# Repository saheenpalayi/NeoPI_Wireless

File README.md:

# Neoπ Wireless CNC Controller (3-axis) 

## Project Overview
This project was made for ESP32 based 3-Axis Milling Machines. I started this project During my time at the FAB LAB Kerala for an awesome project Called [FAB Neo](https://fab.cba.mit.edu/classes/865.21/people/rahul/) by Rahul s Rajan. He was developing an Open source fully compact easy to Use PCB Milling Machine Over the years.

## Fetures of Neoπ Wireless CNC Controller
- NodeMCU-32 ESP32 38 Pin  Board based Controller
- SD Card Supported
- A4988/DRV8825 and SPI TMC 2130 stepper Drivers supported
- Reverse Polarity Protection
- Over Voltage protection**
- 12v/24 compatible
- OTA Supports
- PWM Spindle Support
- 2 Probes available (PROB1 and PROB2)
- Power LED Indications RED(power) and Green (5V)

** Optional The board works even without this feature.

## Hardware Pin Mapping

| Sl No | Pin-Names | GPIO |
| --- | --- | --- |
| 1 | X_Dir | GPIO26 |
| 2 | X_Step | GPIO12 |
| 3 | Y_Dir | GPIO25 |
| 4 | Y_Step | GPIO14 |
| 5 | Z_Dir | GPIO33 |
| 6 | Z_Step | GPIO27 |
| 7 | X_limit | GPIO21 |
| 8 | Y_limit | GPIO4 |
| 9 | Z_limit | GPIO15 |
| 10 | Stepper_disable | GPIO13 |
| 11 | Spindle | GPIO17 |
| 12 | PB1 | GPIO32 |
| 13 | PB2 | GPIO22 |

## Firmware

- Use [Grbl_ESP32](https://github.com/bdring/Grbl_Esp32) with [NeoPI_W_v1.h](https://github.com/saheenpalayi/NeoPI_Wireless/blob/main/Firmware/NeoPI_W_v1.h) machine file

## Credits
The Grbl_ESP32 firmware and the ESP32 Hardware is a well-written Open source Project by [bdring](https://github.com/bdring) A K A Barton Dring.

I took reference from these two projects mentioned below
- [Grbl_ESP32_Development_Controller](https://github.com/bdring/Grbl_ESP32_Development_Controller)
- [A 4 axis ESP32 CNC controller for daisy chained SPI stepper drivers](https://github.com/bdring/4_Axis_SPI_CNC#revision-history)
## Revision History
**v1.0**
- version 1 is my first build it has some problems and fixes to do

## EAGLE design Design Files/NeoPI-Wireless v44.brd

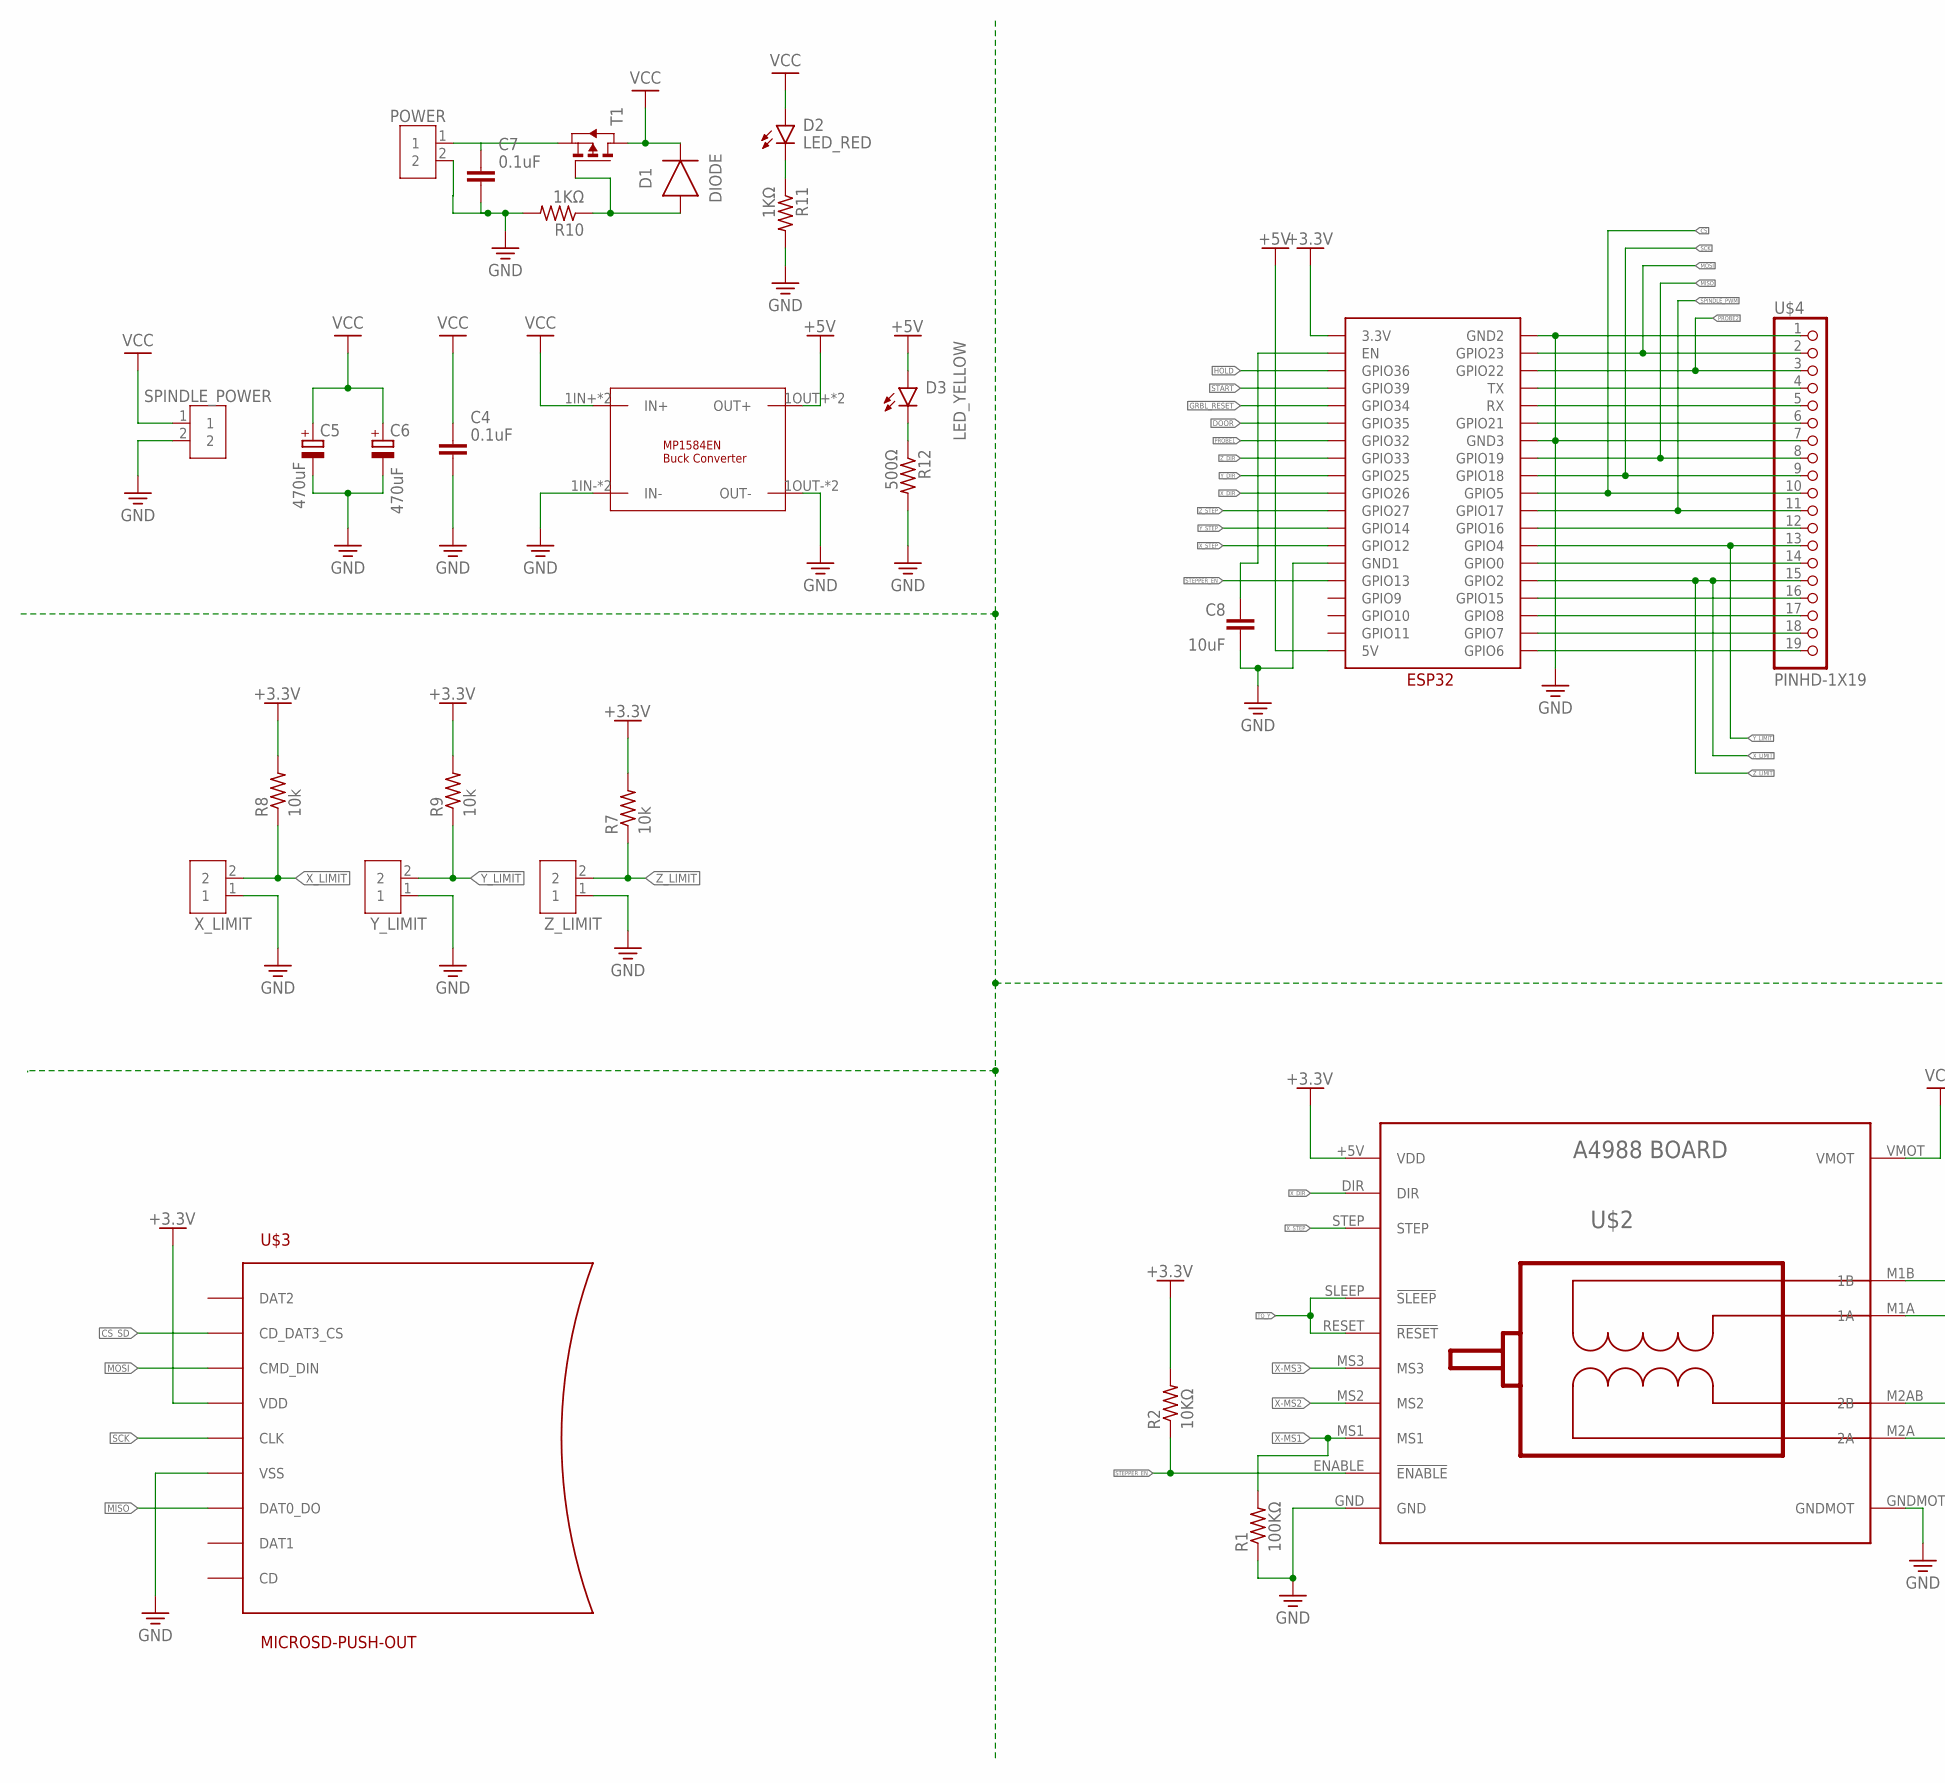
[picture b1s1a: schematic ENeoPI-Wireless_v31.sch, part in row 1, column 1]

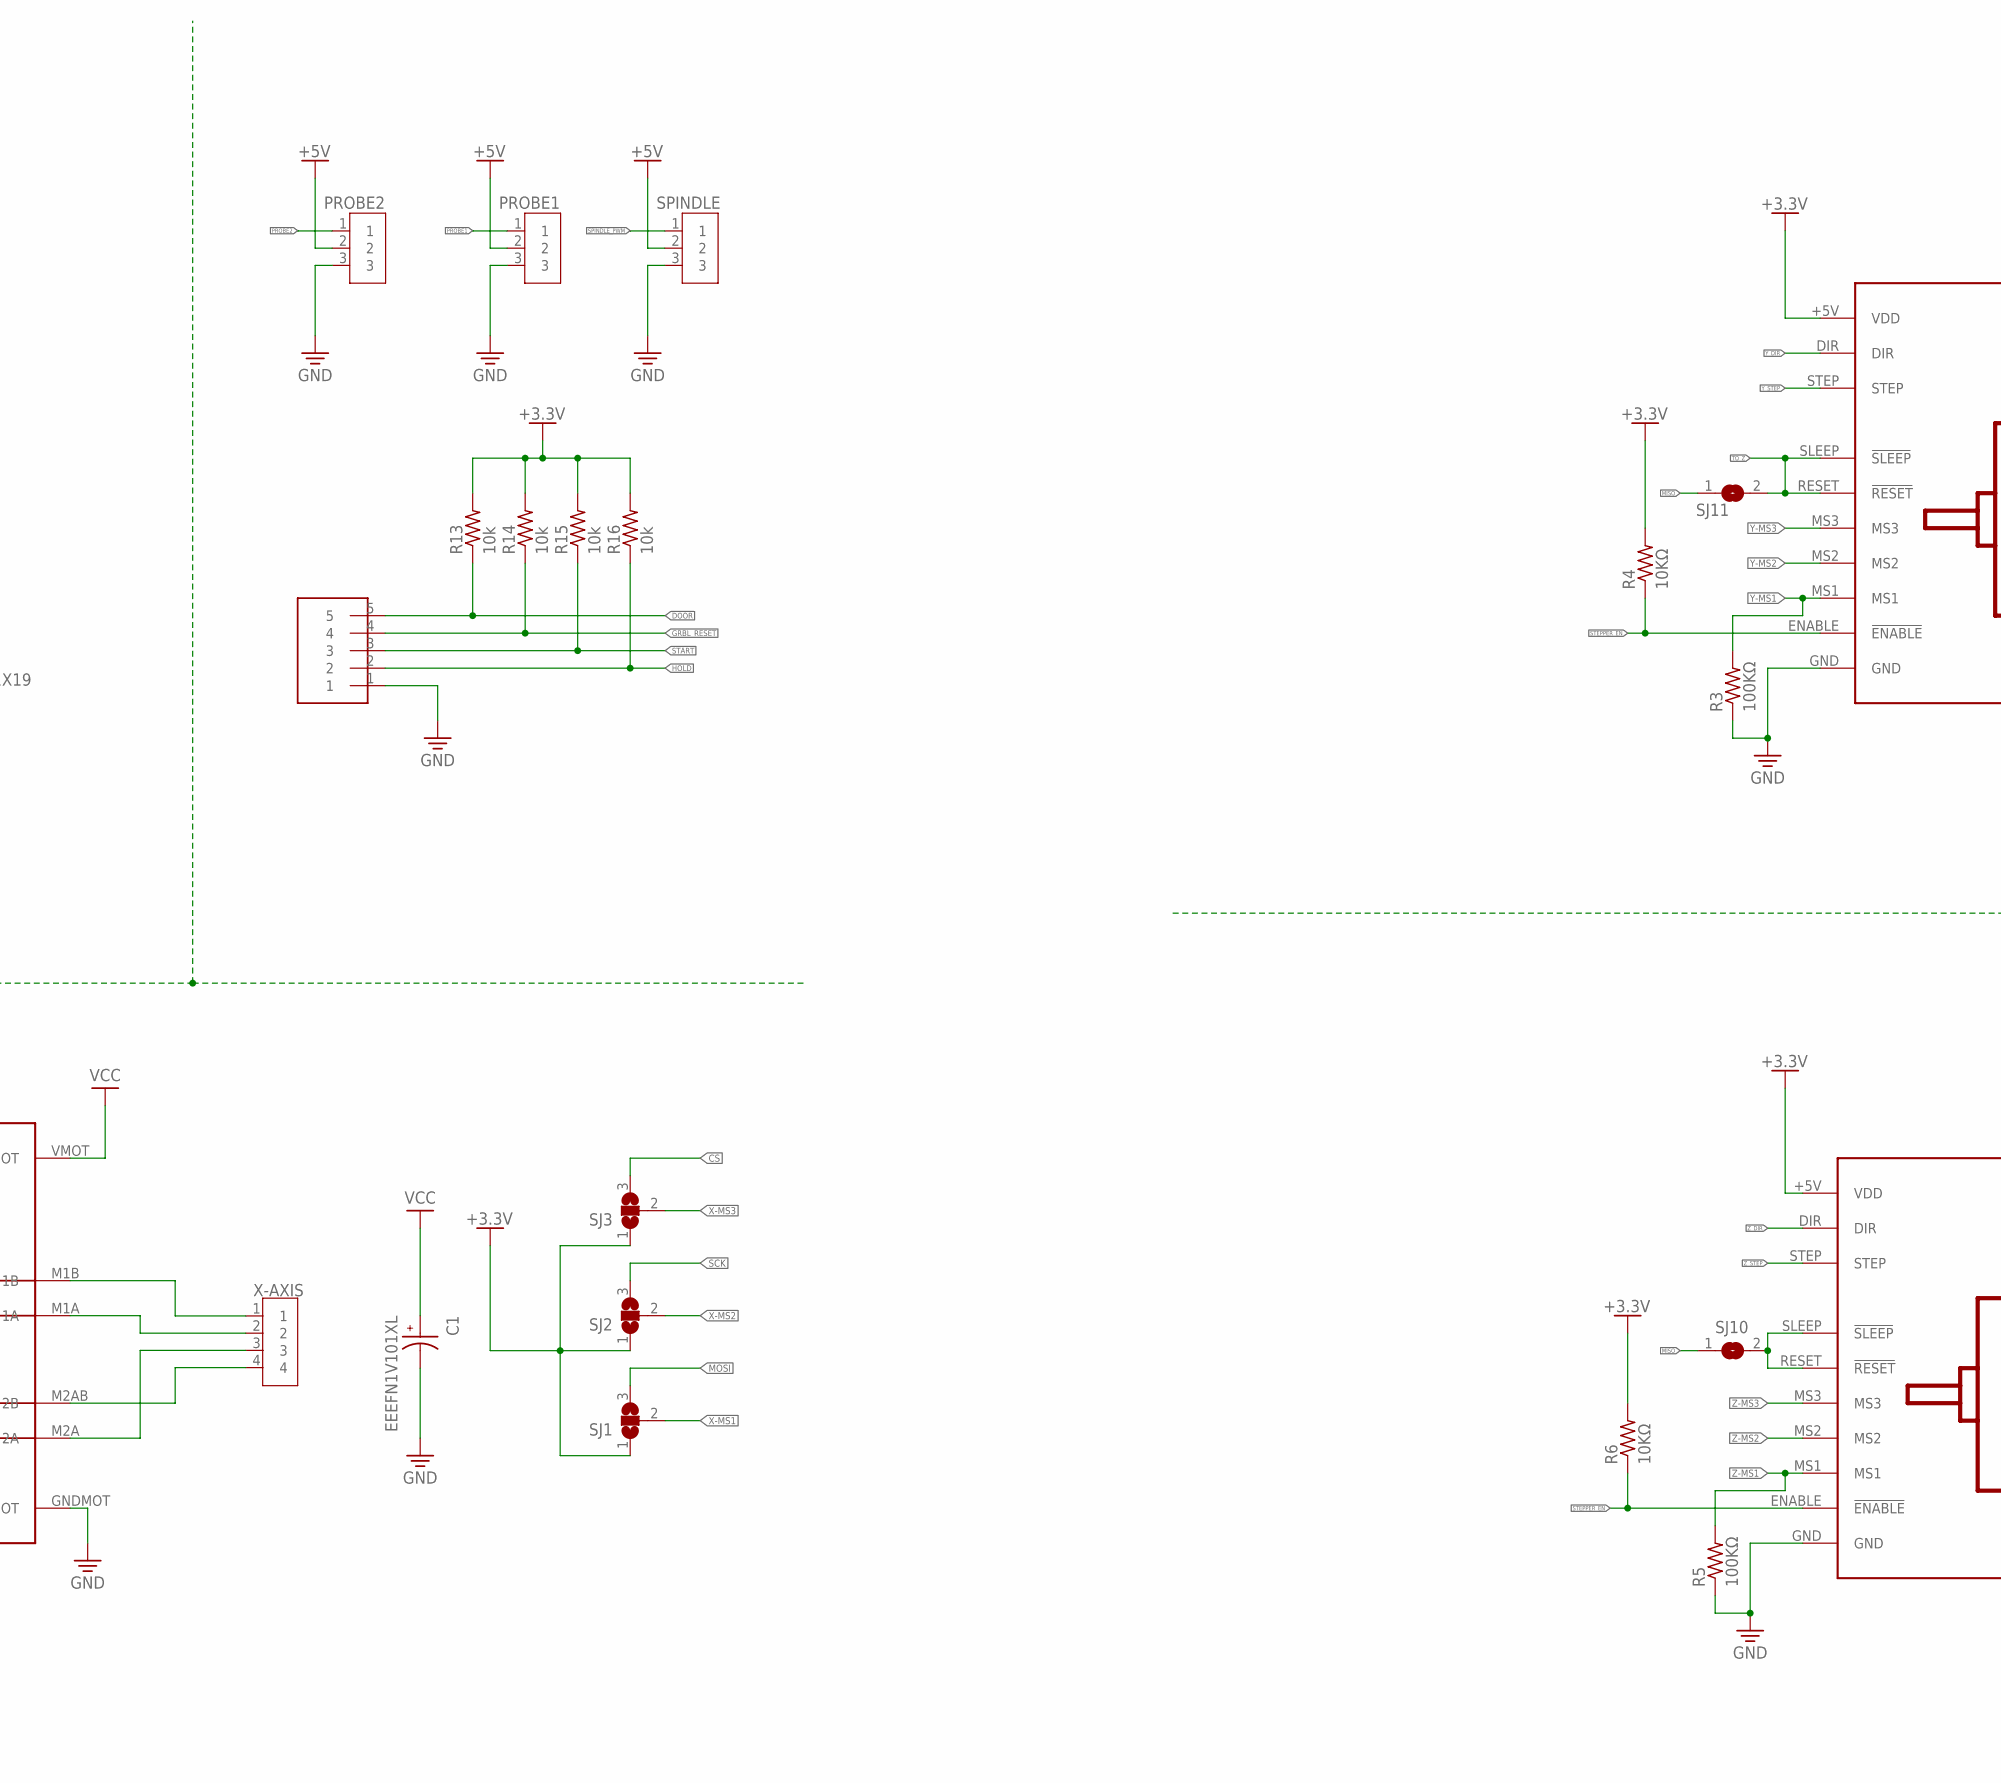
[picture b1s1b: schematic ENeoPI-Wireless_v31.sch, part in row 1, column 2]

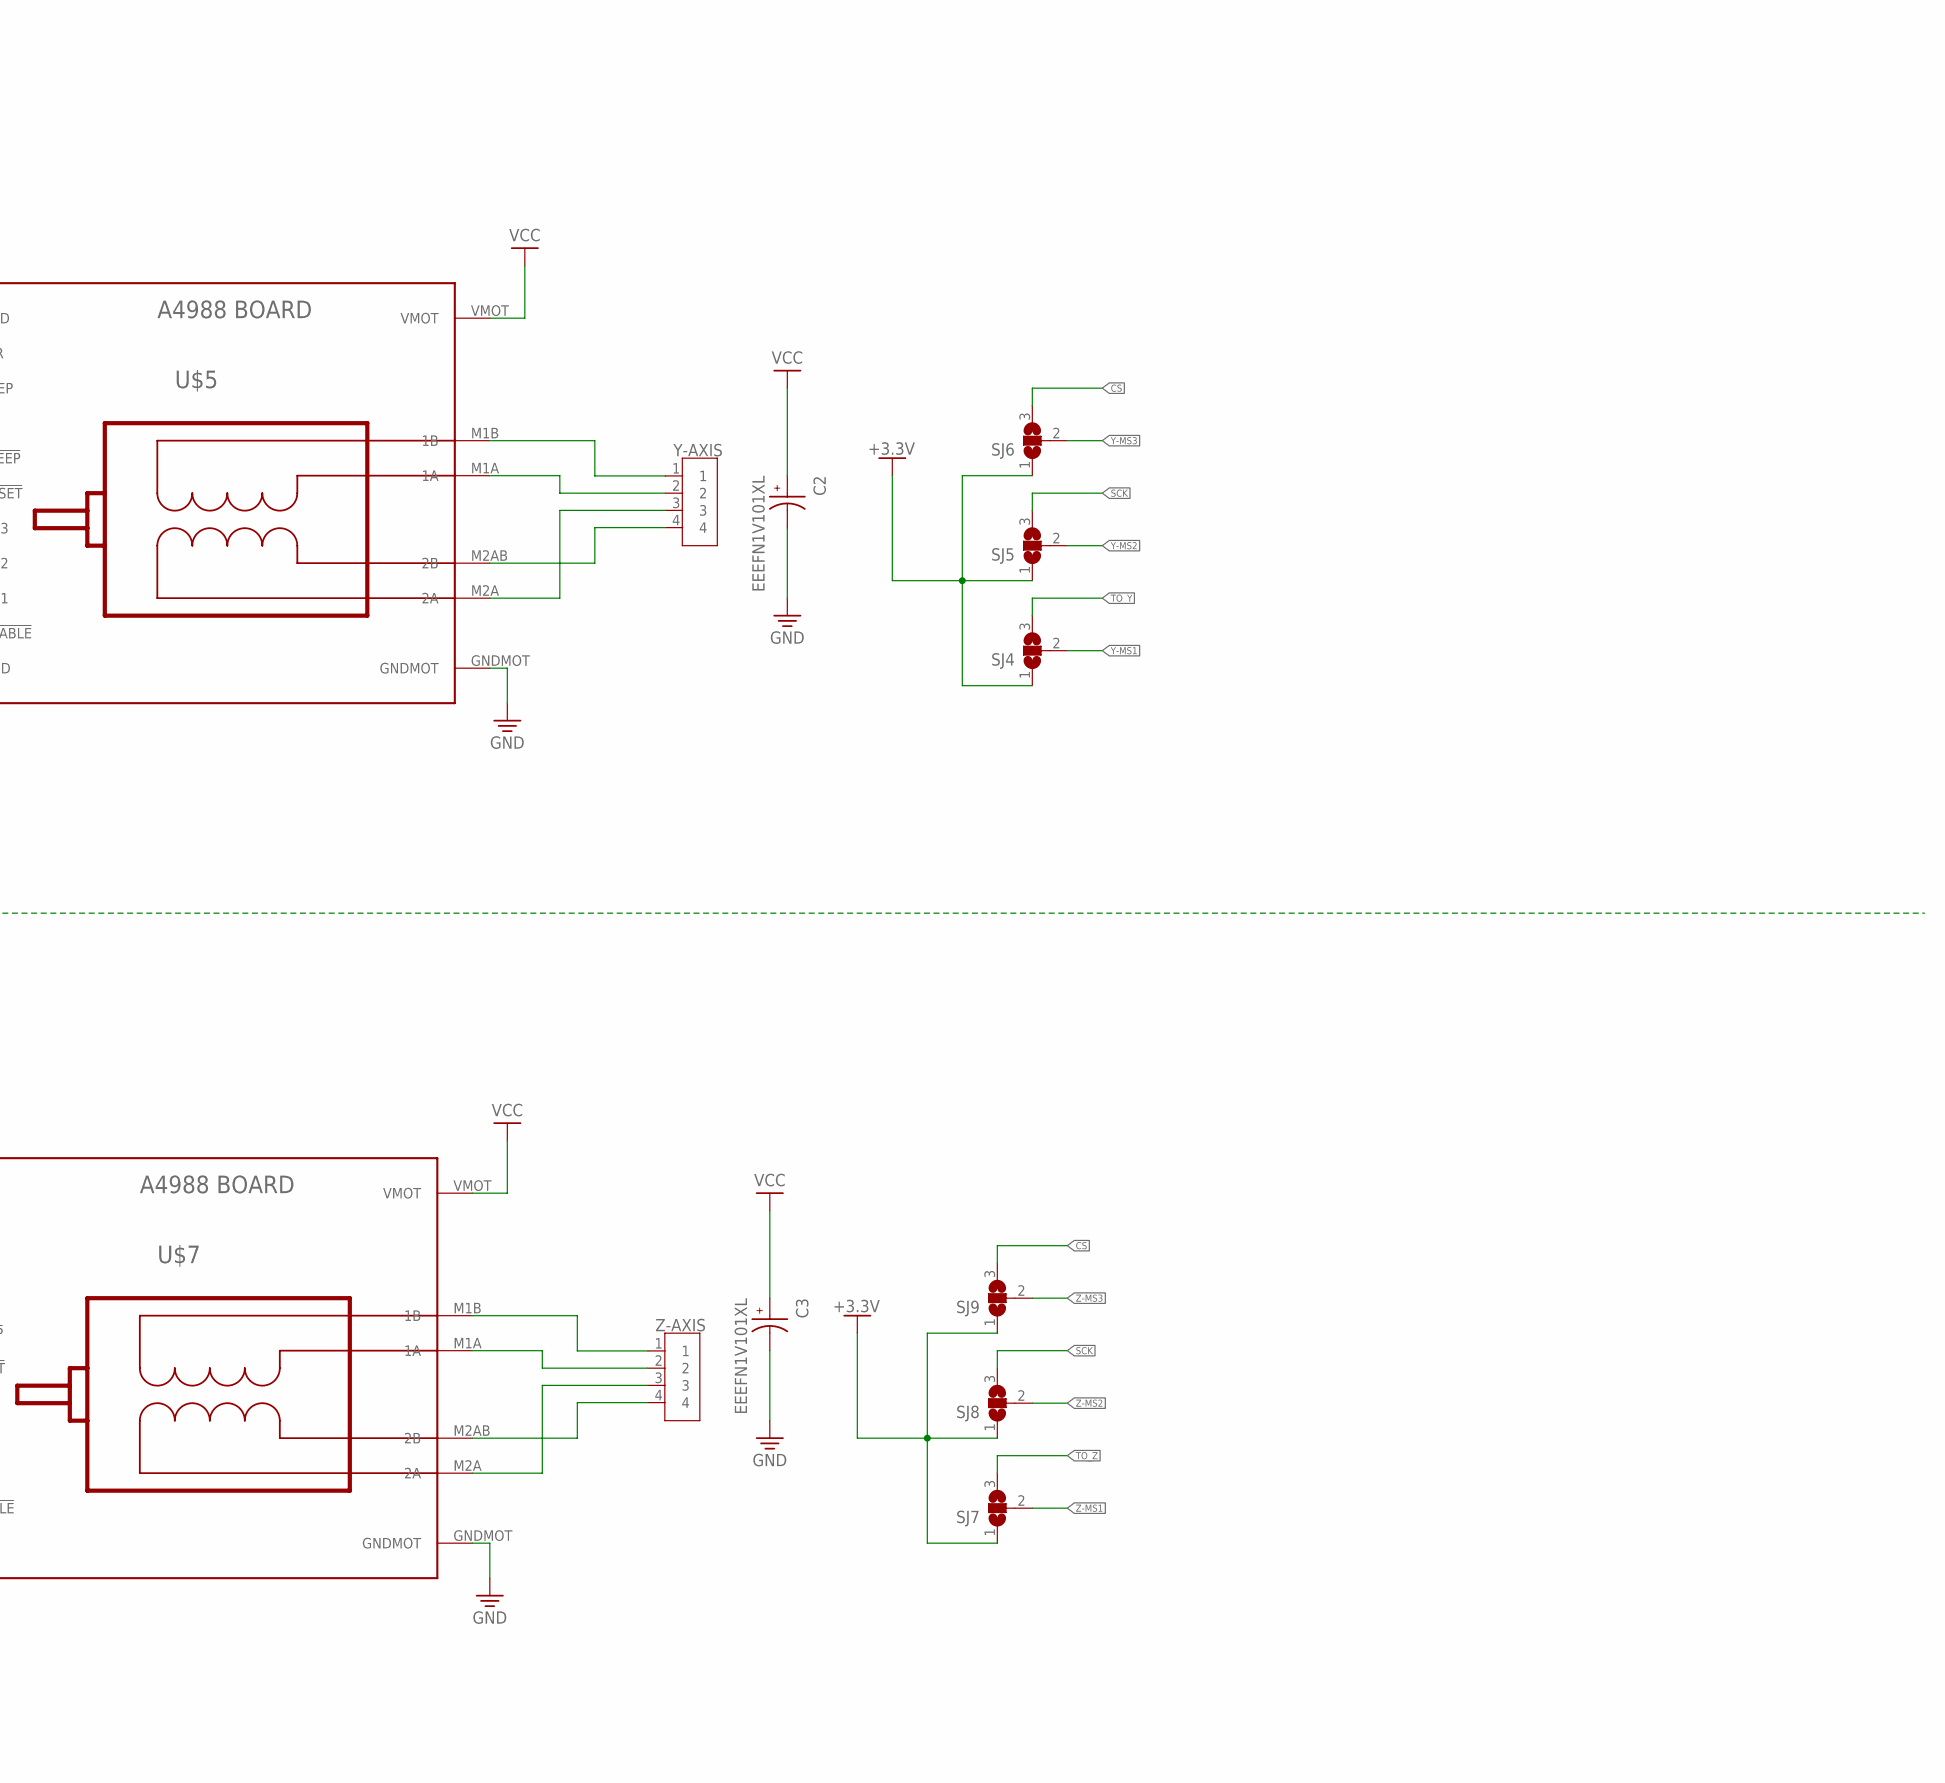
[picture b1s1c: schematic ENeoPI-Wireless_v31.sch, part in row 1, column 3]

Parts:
C1, C2, C3: EEEFN1V101XL; CAP_EEEFN1V101XL
C4, C7: 0.1uF; CAPC3216X135
C5, C6: 470uF; CAPAE1030X1050N
C8: 10uF; CAPC3216X135
D1: DIODE; DIOMELF5024
D2: LED_RED; LEDC3216X75N_FLAT-R
D3: LED_YELLOW; LEDC3216X75N_FLAT-Y
POWER: 2828XX-2282837-2; TERMBLK_508-2N
PROBE1, PROBE2: 2828XX-3282834-3; TERMBLK_254-3N
R1, R3, R5: 100KΩ; R1206FAB
R2, R4, R6: 10KΩ; R1206FAB
R7, R8, R9, R13, R14, R15, R16: 10k; R1206FAB
R10, R11: 1KΩ; R1206FAB
R12: 500Ω; R1206FAB
SJ1, SJ2, SJ3, SJ4, SJ5, SJ6, SJ7, SJ8, SJ9: SJ2W; SJ_2
SJ10, SJ11: SJ
SPINDLE: 2828XX-3282834-3; TERMBLK_254-3N
SPINDLE_POWER: 2828XX-2282837-2; TERMBLK_508-2N
T1: PMOSFET; TO252
U$1: ESP32_GRBL
U$2, U$5, U$7: BOARD_A4988
U$3: MICROSD-PUSH-OUT
U$4: PINHD-1X19; 1X19
U$6: MINI-360_DC-TO-DC_BUCK_CONVERTER; MINI_BUCK_CONVERTER
U$8: 1X05_SMD
X-AXIS: 2828XX-4282837-4; TERMBLK_508-4N
X_LIMIT: 2828XX-2282834-2; TERMBLK_254-2N
Y-AXIS: 2828XX-4282837-4; TERMBLK_508-4N
Y_LIMIT: 2828XX-2282834-2; TERMBLK_254-2N
Z-AXIS: 2828XX-4282837-4; TERMBLK_508-4N
Z_LIMIT: 2828XX-2282834-2; TERMBLK_254-2N

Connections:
+3.3V: R2.2, R4.2, R6.2, R7.2, R8.2, R9.2, R13.2, R14.2, R15.2, R16.2, SJ1.1, SJ2.1, SJ3.1, SJ4.1, SJ5.1, SJ6.1, SJ7.1, SJ8.1, SJ9.1, U$1.3.3V, U$2.+5V (VDD), U$3.4 (VDD), U$5.+5V (VDD), U$7.+5V (VDD)
+5V: D3.A, PROBE1.2, PROBE2.2, SPINDLE.2, U$1.5V, U$6.1OUT+ (OUT+), U$6.2OUT+ (OUT+)
CS: SJ3.3, SJ6.3, SJ9.3, U$1.GPIO5, U$4.10
CS_SD: U$3.2 (CD_DAT3_CS)
DOOR: R13.1, U$1.GPIO35, U$8.5
GND: C1.2, C2.2, C3.2, C4.2, C5.2 (-), C6.2 (-), C7.2, C8.2, POWER.2, PROBE1.3, PROBE2.3, R1.1, R3.1, R5.1, R10.2, R11.2, R12.2, SPINDLE.3, SPINDLE_POWER.2, U$1.GND1, U$1.GND2, U$1.GND3, U$2.GND, U$2.GNDMOT, U$3.6 (VSS), U$3.G1 (VSS), U$3.G2 (VSS), U$3.G3 (VSS), U$3.G4 (VSS), U$4.1, U$4.7, U$5.GND, U$5.GNDMOT, U$6.1IN- (IN-), U$6.1OUT- (OUT-), U$6.2IN- (IN-), U$6.2OUT- (OUT-), U$7.GND, U$7.GNDMOT, U$8.1, X_LIMIT.1, Y_LIMIT.1, Z_LIMIT.1
GRBL_RESET: R14.1, U$1.GPIO34, U$8.4
HOLD: R16.1, U$1.GPIO36, U$8.2
MISO: SJ10.1, SJ11.1, U$1.GPIO19, U$3.7 (DAT0_DO), U$4.8
MOSI: SJ1.3, U$1.GPIO23, U$3.3 (CMD_DIN), U$4.2
unnamed: U$2.M1B (1B), X-AXIS.1
unnamed: U$2.M1A (1A), X-AXIS.2
unnamed: U$2.M2A (2A), X-AXIS.3
unnamed: U$2.M2AB (2B), X-AXIS.4
unnamed: U$1.TX, U$4.4
unnamed: D2.C, R11.1
unnamed: U$1.GPIO21, U$4.6
unnamed: U$5.M1B (1B), Y-AXIS.1
unnamed: U$5.M1A (1A), Y-AXIS.2
unnamed: D3.C, R12.1
unnamed: C8.1, U$1.EN
unnamed: U$5.M2A (2A), Y-AXIS.3
unnamed: U$5.M2AB (2B), Y-AXIS.4
unnamed: U$7.M1B (1B), Z-AXIS.1
unnamed: U$7.M1A (1A), Z-AXIS.2
unnamed: SJ10.2, U$7.RESET (!RESET), U$7.SLEEP (!SLEEP)
unnamed: U$7.M2A (2A), Z-AXIS.3
unnamed: U$7.M2AB (2B), Z-AXIS.4
unnamed: U$1.RX, U$4.5
unnamed: U$1.GPIO16, U$4.12
unnamed: C7.1, POWER.1, T1.2 (S)
unnamed: U$1.GPIO0, U$4.14
unnamed: U$1.GPIO8, U$4.17
unnamed: U$1.GPIO7, U$4.18
unnamed: U$1.GPIO6, U$4.19
unnamed: D1.2 (A), R10.1, T1.1 (G)
PROBE1: PROBE1.1, U$1.GPIO32
PROBE2: PROBE2.1, U$1.GPIO22, U$4.3
SCK: SJ2.3, SJ5.3, SJ8.3, U$1.GPIO18, U$3.5 (CLK), U$4.9
SPINDLE_PWM: SPINDLE.1, U$1.GPIO17, U$4.11
START: R15.1, U$1.GPIO39, U$8.3
STEPPER_EN: R2.1, R4.1, R6.1, U$1.GPIO13, U$2.ENABLE (!ENABLE), U$5.ENABLE (!ENABLE), U$7.ENABLE (!ENABLE)
TO_Y: SJ4.3, U$2.RESET (!RESET), U$2.SLEEP (!SLEEP)
TO_Z: SJ7.3, SJ11.2, U$5.RESET (!RESET), U$5.SLEEP (!SLEEP)
VCC: C1.1, C2.1, C3.1, C4.1, C5.1 (+), C6.1 (+), D1.1 (C), D2.A, SPINDLE_POWER.1, T1.3 (D), U$2.VMOT, U$5.VMOT, U$6.1IN+ (IN+), U$6.2IN+ (IN+), U$7.VMOT
X-MS1: R1.2, SJ1.2, U$2.MS1
X-MS2: SJ2.2, U$2.MS2
X-MS3: SJ3.2, U$2.MS3
X_DIR: U$1.GPIO26, U$2.DIR
X_LIMIT: R8.1, U$1.GPIO2, U$4.15, X_LIMIT.2
X_STEP: U$1.GPIO12, U$2.STEP
Y-MS1: R3.2, SJ4.2, U$5.MS1
Y-MS2: SJ5.2, U$5.MS2
Y-MS3: SJ6.2, U$5.MS3
Y_DIR: U$1.GPIO25, U$5.DIR
Y_LIMIT: R9.1, U$1.GPIO4, U$4.13, Y_LIMIT.2
Y_STEP: U$1.GPIO14, U$5.STEP
Z-MS1: R5.2, SJ7.2, U$7.MS1
Z-MS2: SJ8.2, U$7.MS2
Z-MS3: SJ9.2, U$7.MS3
Z_DIR: U$1.GPIO33, U$7.DIR
Z_LIMIT: R7.1, U$1.GPIO15, U$4.16, Z_LIMIT.2
Z_STEP: U$1.GPIO27, U$7.STEP

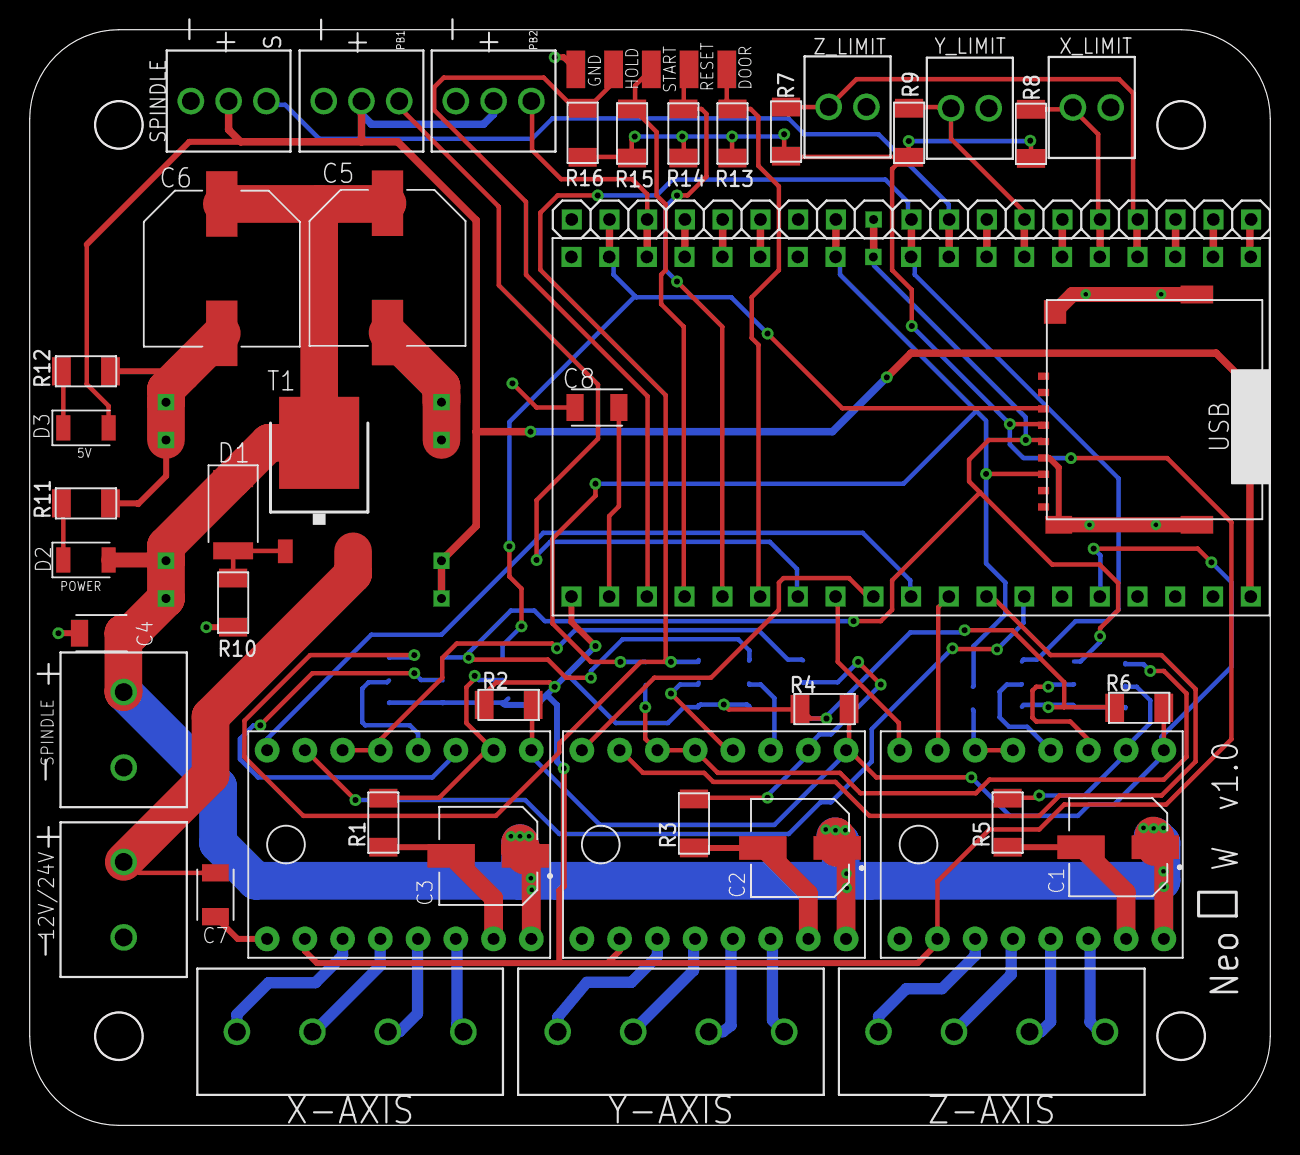
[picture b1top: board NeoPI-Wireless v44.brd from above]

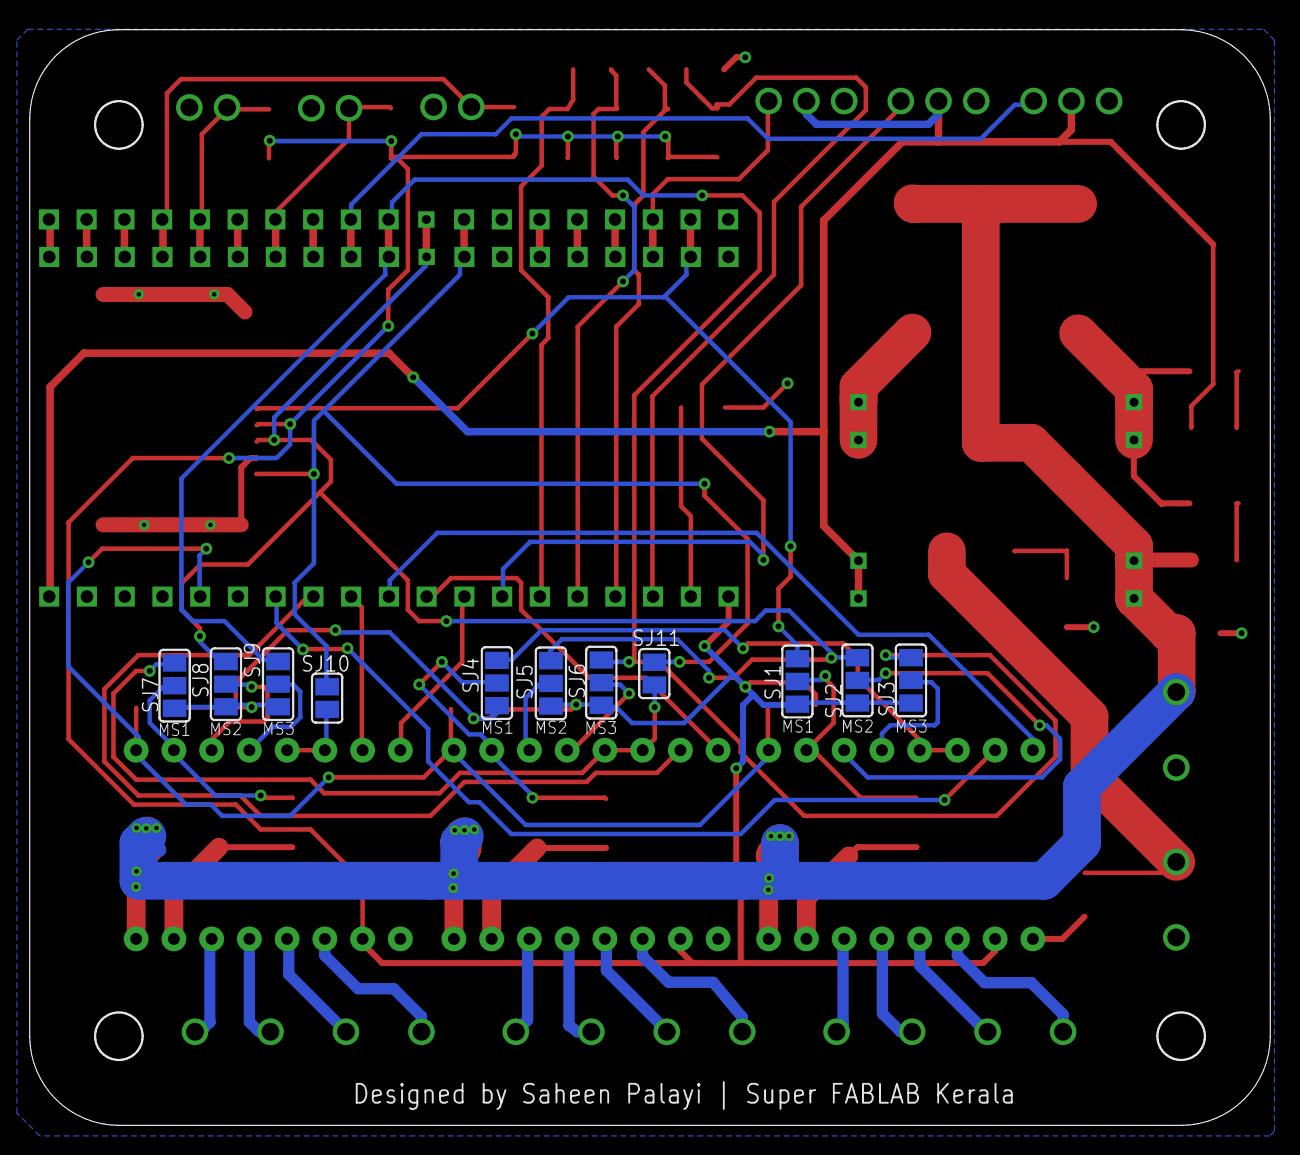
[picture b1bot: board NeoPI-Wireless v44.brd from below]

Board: 2 copper layers, 83.3 x 73.6 mm, 58 parts (11 on the bottom side), 62 nets.

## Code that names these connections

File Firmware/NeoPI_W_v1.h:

#pragma once
// clang-format off

/*
    NeoPI_W_v1.h
    Part of Grbl_ESP32

    Pin assignments for the NeoPI Wireless CNC Controller(3-axis), v1.0 and later.
    https://github.com/saheenpalayi/NeoPI_Wireless

    2018    - Bart Dring
    2020    - Mitch Bradley
    2022    - Saheen Palayi

    Grbl_ESP32 is free software: you can redistribute it and/or modify
    it under the terms of the GNU General Public License as published by
    the Free Software Foundation, either version 3 of the License, or
    (at your option) any later version.

    Grbl is distributed in the hope that it will be useful,
    but WITHOUT ANY WARRANTY; without even the implied warranty of
    MERCHANTABILITY or FITNESS FOR A PARTICULAR PURPOSE.  See the
    GNU General Public License for more details.

    You should have received a copy of the GNU General Public License
    along with Grbl_ESP32.  If not, see <http://www.gnu.org/licenses/>.
*/

#define MACHINE_NAME            "NeoPI_W_v1"

#define X_STEP_PIN              GPIO_NUM_12
#define X_DIRECTION_PIN         GPIO_NUM_26
#define Y_STEP_PIN              GPIO_NUM_14
#define Y_DIRECTION_PIN         GPIO_NUM_25
#define Z_STEP_PIN              GPIO_NUM_27
#define Z_DIRECTION_PIN         GPIO_NUM_33

#define X_LIMIT_PIN             GPIO_NUM_2
#define Y_LIMIT_PIN             GPIO_NUM_4
#define Z_LIMIT_PIN             GPIO_NUM_15


// OK to comment out to use pin for other features
#define STEPPERS_DISABLE_PIN    GPIO_NUM_13

#define SPINDLE_TYPE            SpindleType::BESC
#define SPINDLE_OUTPUT_PIN      GPIO_NUM_17   // labeled SpinPWM
// #define SPINDLE_ENABLE_PIN      GPIO_NUM_22  // labeled SpinEnbl

// #define COOLANT_MIST_PIN        GPIO_NUM_21  // labeled Mist
// #define COOLANT_FLOOD_PIN       GPIO_NUM_25  // labeled Flood
#define PROBE_PIN               GPIO_NUM_32  // labeled Probe


/*
#define CONTROL_SAFETY_DOOR_PIN GPIO_NUM_35  // labeled Door,  needs external pullup
#define CONTROL_RESET_PIN       GPIO_NUM_34  // labeled Reset, needs external pullup
#define CONTROL_FEED_HOLD_PIN   GPIO_NUM_36  // labeled Hold,  needs external pullup
#define CONTROL_CYCLE_START_PIN GPIO_NUM_39  // labeled Start, needs external pullup
*/

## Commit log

2022-10-06 Readme update and fixes
    Fixed some issues in schematic
2022-10-06 Readme update
    added backlink
2022-10-09 doc-updates
    firmware folder added with .h file
    image of fully assembled PCB Added
2022-10-09 Doc-update
    documentation-update
2022-10-09 update
    doc and heeder file edited
2025-04-13 added pin mapping table
2025-04-21 firmware added for velichapad
2025-04-21 added zip file of the firmware
